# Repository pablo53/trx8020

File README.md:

# trx8020 - KiCAD project
Transceiver 80m 20m

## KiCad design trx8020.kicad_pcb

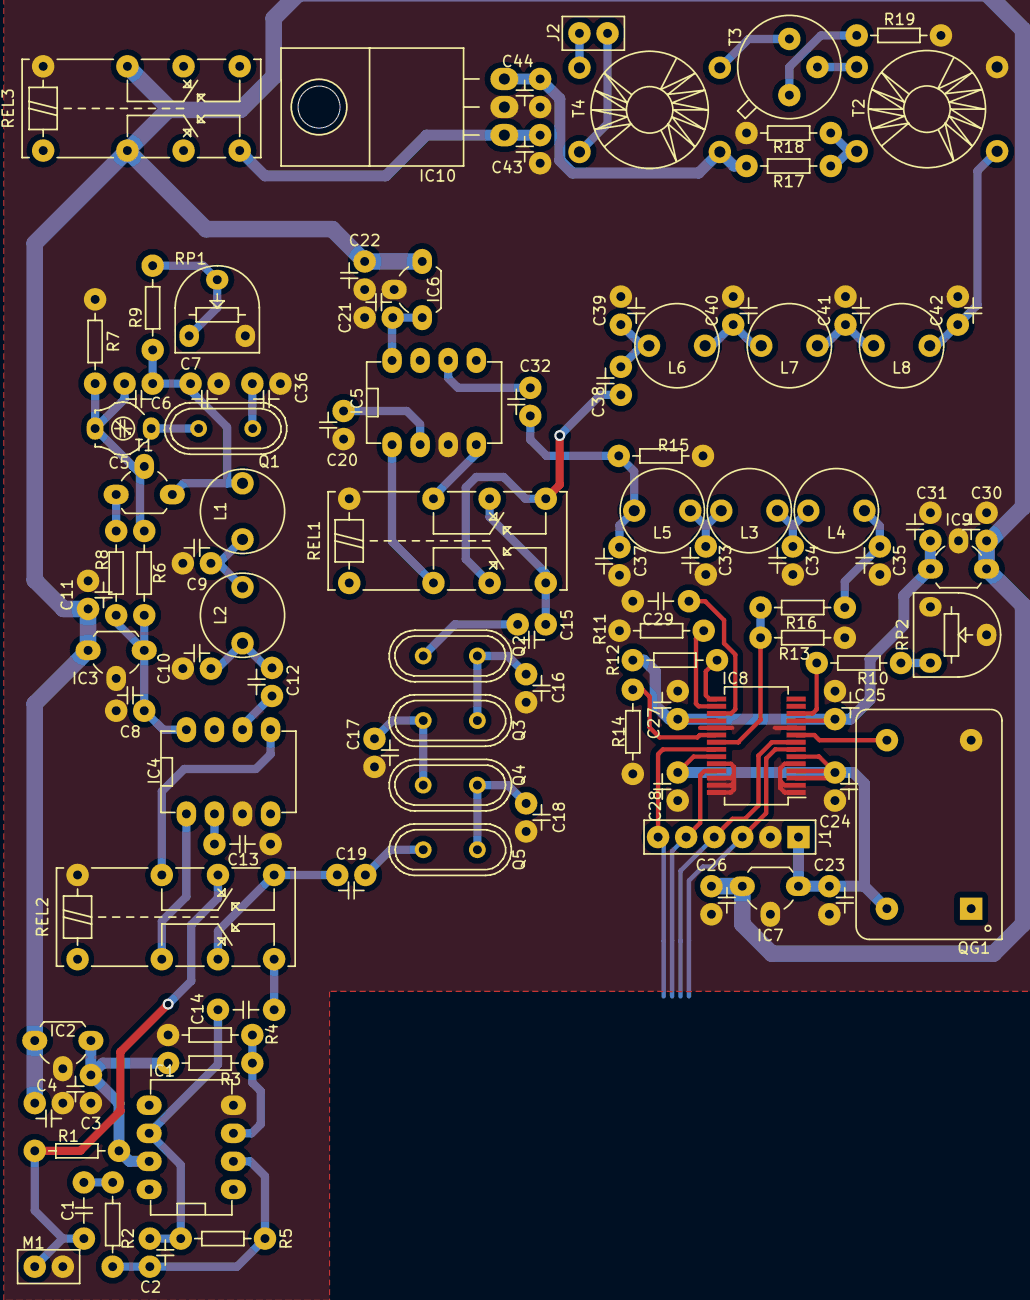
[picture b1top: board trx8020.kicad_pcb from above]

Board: 2 copper layers, 99 parts (0 on the bottom side), 66 nets.

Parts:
C1, C13, C14: 1u; C2
C2, C3, C4, C8, C11, C12, C20, C21, C23, C24, C25, C27, C28, C31, C32, C43: 100n; C1
C5: 6-22p; C2Trim
C6, C7: 220p; C1
C9: 33p; C1
C10, C36: 10p; C1
C15, C16, C17, C18, C19: 68p; C1
C22, C26, C30: 1u; C1
C29: 10u; C2
C33, C34: 47p; C1
C35, C37: 27p; C1
C38: 100nF; C1
C39, C42: 22p; C1
C40, C41: 39p; C1
C44: 10n; C1
IC1: NE5534; DIP-8
IC2: 78L10; TO-92
IC3, IC6: 78L06; TO-92
IC4, IC5: SA612; DIP-8
IC7, IC9: 78L05; TO-92
IC8: AD9850; SSOP-28
IC10: 7812; TO-220
J1: Pin_1x6
J2: DRV_OUT; Pin_1x2
L1, L2: 47u; Inductor
L3, L4, L5: 3.3u; Inductor
L6, L8: 56u; Inductor
L7: 68u; Inductor
M1: Mic; Pin_1x2
Q1: 6 MHz; HC49-U
Q2, Q3, Q4, Q5: 6MHz; HC49-U
QG1: 125 MHz; KXO-200
R1: 47k; R3
R2: 2k2; R3
R3, R4: 10k; R3
R5: 220k; R3
R6: 100k; R3
R7: 680k; R3
R8, R13, R14: 100; R3
R9, R11, R12: 1k; R3
R10: 3k9; R3
R15, R16: 390; R3
R17: 1k2; R3
R18: 150; R3
R19: 10; R3
REL1, REL2, REL3: AZ822-2C; AZ822
RP1, RP2: 10k; RM-065
T1: BC-547; TO-92
T2: 30t:8t; Transformer2_Amidon-T37
T3: 2N2219; TO-39
T4: 1:2; Transformer2_Amidon-T37

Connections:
/DAT: IC8.25, J1.5
/FQUD: IC8.8, J1.4
/RST: IC8.22, J1.6
/WCLK: IC8.7, J1.3
GND: C3.1, C4.1, C7.1, C8.1, C9.1, C10.1, C11.1, C13.1, C16.2, C17.2, C18.2, C20.1, C21.1, C22.1, C23.2, C24.2, C25.1, C26.2, C27.2, C28.1, C29.2, C30.2, C31.2, C33.1, C34.1, C35.1, C36.1, C37.1, C39.1, C40.1, C41.1, C42.1, C43.1, C44.1, IC1.4, IC2.2, IC3.2, IC4.3, IC5.3, IC6.2, IC7.2, IC8.1, IC8.2, IC8.5, IC8.10, IC8.19, IC8.24, IC8.26, IC8.27, IC8.28, IC9.2, IC10.2, J1.2, M1.2, QG1.7, R4.1, R7.1, R11.2, R13.2, R14.2, R15.1, R18.1, R19.1, REL1.16, REL2.16, REL3.16, RP1.1, RP2.2, RP2.3, T2.1
unnamed: C1.1, M1.1, R1.1, REL2.11
unnamed: C1.2, R2.1
unnamed: C2.2, IC1.2, R2.2, R5.1
unnamed: C3.2, IC1.7, IC2.1, R1.2, R3.2
unnamed: C5.1, Q1.2
unnamed: C5.2, C6.2, R6.1, R7.2, T1.2
unnamed: C6.1, C7.2, L1.1, R9.2, T1.3
unnamed: C8.2, IC3.1, IC4.8, R6.2, R8.2
unnamed: C9.2, L1.2, L2.1
unnamed: C10.2, C12.2, L2.2
unnamed: C12.1, IC4.6
unnamed: C13.2, IC4.2
unnamed: C2.1, C14.1, IC1.6, R5.2
unnamed: C14.2, REL2.8
unnamed: C15.1, REL1.8, REL1.11
unnamed: C15.2, Q2.1
unnamed: C16.1, Q2.2, Q3.1
unnamed: C17.1, Q3.2, Q4.1
unnamed: C18.1, Q4.2, Q5.1
unnamed: C19.1, Q5.2
unnamed: C19.2, REL2.6, REL2.9
unnamed: C20.2, IC5.2
unnamed: C21.2, IC5.8, IC6.1
unnamed: C23.1, C24.1, C28.2, IC7.1, IC8.3, IC8.4, IC8.6, IC8.23, J1.1, QG1.14
unnamed: C25.2, C27.1, C31.1, IC8.11, IC8.18, IC9.1, R12.2
unnamed: C29.1, IC8.17
unnamed: C32.1, C37.2, L5.1, R15.2
unnamed: C32.2, IC5.6
unnamed: C33.2, L3.1, L5.2
unnamed: C34.2, L3.2, L4.1
unnamed: C35.2, L4.2, R16.1
unnamed: C36.2, Q1.1
unnamed: C38.1, REL1.6, REL1.9
unnamed: C38.2, C39.2, L6.1
unnamed: C40.2, L6.2, L7.1
unnamed: C41.2, L7.2, L8.1
unnamed: C42.2, L8.2, T2.3
unnamed: C43.2, IC10.1, REL3.8
unnamed: C44.2, IC10.3, R17.2, T4.3
unnamed: IC1.3, R3.1, R4.2
unnamed: IC4.1, REL2.4
unnamed: IC4.5, REL2.13
unnamed: IC5.1, REL1.4
unnamed: IC5.4, REL1.13
unnamed: IC8.9, QG1.8
unnamed: IC8.12, R10.2
unnamed: IC8.15, R12.1
unnamed: IC8.16, R11.1
unnamed: IC8.20, R14.1
unnamed: IC8.21, R13.1, R16.2
unnamed: J2.1, T4.2
unnamed: J2.2, T4.4
unnamed: R8.1, T1.1
unnamed: R9.1, RP1.2, RP1.3
unnamed: R10.1, RP2.1
unnamed: R17.1, R18.2, T2.4
unnamed: R19.2, T3.3
unnamed: T2.2, T3.2
unnamed: T3.1, T4.1
PTT: REL1.1, REL2.1, REL3.1
PWR: C4.2, C11.2, C22.2, C26.1, C30.1, IC2.3, IC3.3, IC6.3, IC7.3, IC9.3, REL3.4, REL3.13

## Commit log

2021-06-28 sine wave gen, mic preamp
2021-07-01 mixer II...
2021-07-11 minor fix
2021-07-26 relays
2021-07-28 driver
